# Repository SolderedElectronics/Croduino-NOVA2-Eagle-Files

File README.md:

# Croduino NOVA2 Eagle Files
## Image

[Croduino NOVA(222067)](https://e-radionica.com/en/croduino-nova2.html)

## Description and details
The Croduino NOVA2 is a microcontroller board with the ability to connect to a WiFi network and the Internet! It is based on an already well-known ESP8266 which is otherwise quite complicated to use on its own. With Nova, simply connect the board to USB and start programming your next IoT project. In addition, the microcontroller boards ideally suited for breadboard, which makes prototyping is even faster. Connecting the physical world with the internet has never been easier.

The brain of these boards is already mentioned Espressif's ESP826. Comes with full WiFi (both client and server side) and an integrated TCP / IP stack that supports DNS! Most importantly - programmable from Arduino IDE, there is no need to manually reset the board. The 80MHz frequency processor has as much as 1MB of space for your code (0.8MB available, bootloader 0.2MB) and 82kB of RAM (of which you can use 49kB). The board supports I2C, SPI and serial communications and has 9 GPIO pins, all of which support PWM and one analog input. In addition to the above, the board uses CH340 as a USB 2.0 interface, 3.3V voltage regulator, 4 LEDs, FCC and CE certificate, and a lot more. There is also an easyC connector on the board, which allows easy connection of various devices (available in e-radionica's offer) with a board. Finally, there is a standard JST lithium-ion connector for your project to be truly wireless. When you need to charge a battery, just plug in the USB cable and charge the battery with the integrated charger on the board. In detail:

- ESP8266 in ESP-12 package
- 80MHz, 1MB flash, 82kB RAM
- programmable from Arduina!
- 9 GPIO pins of which all support PWM
- 1 analog input(ADC), max. voltage 1V i 5V
- I2C, SPI, serial communication
- CH340 USB to UART bridge with micro USB connector
- 3.3V voltage regulator
- LEDs: power, tx, rx, GPIO13
- automatical hardware reset before upload of code
- two pushbuttons: reset i GPIO0
- comes with micro USB cable
- FCC i CE certificates for ESP-12

ESP8266 on-board is loaded with default bootloader.

## Repository content
This repo contains Cadsoft Eagle .sch and .brd files for Croduino NOVA board. It also contains schematic in .pdf created from .sch Eagle file. 
Files have been arranged into folders for navigating between different versions of board. 
Tip: layer 200 shows top silkscreen and layer 208 should be bottom silkscreen. tParts and bParts layers are not used.

## Docs
- [Croduino NOVA 2product page] (https://e-radionica.com/en/croduino-nova2.html)

## Board versions
- v1.0 - inital published version 

## License info
This product is open-source. Yay!
For any tech questions, contact us at techsupport@e-radionica.com
If you find an Issue, please open one at GitHub. If you can improve our product, fork us.

e-radionica.com Team.

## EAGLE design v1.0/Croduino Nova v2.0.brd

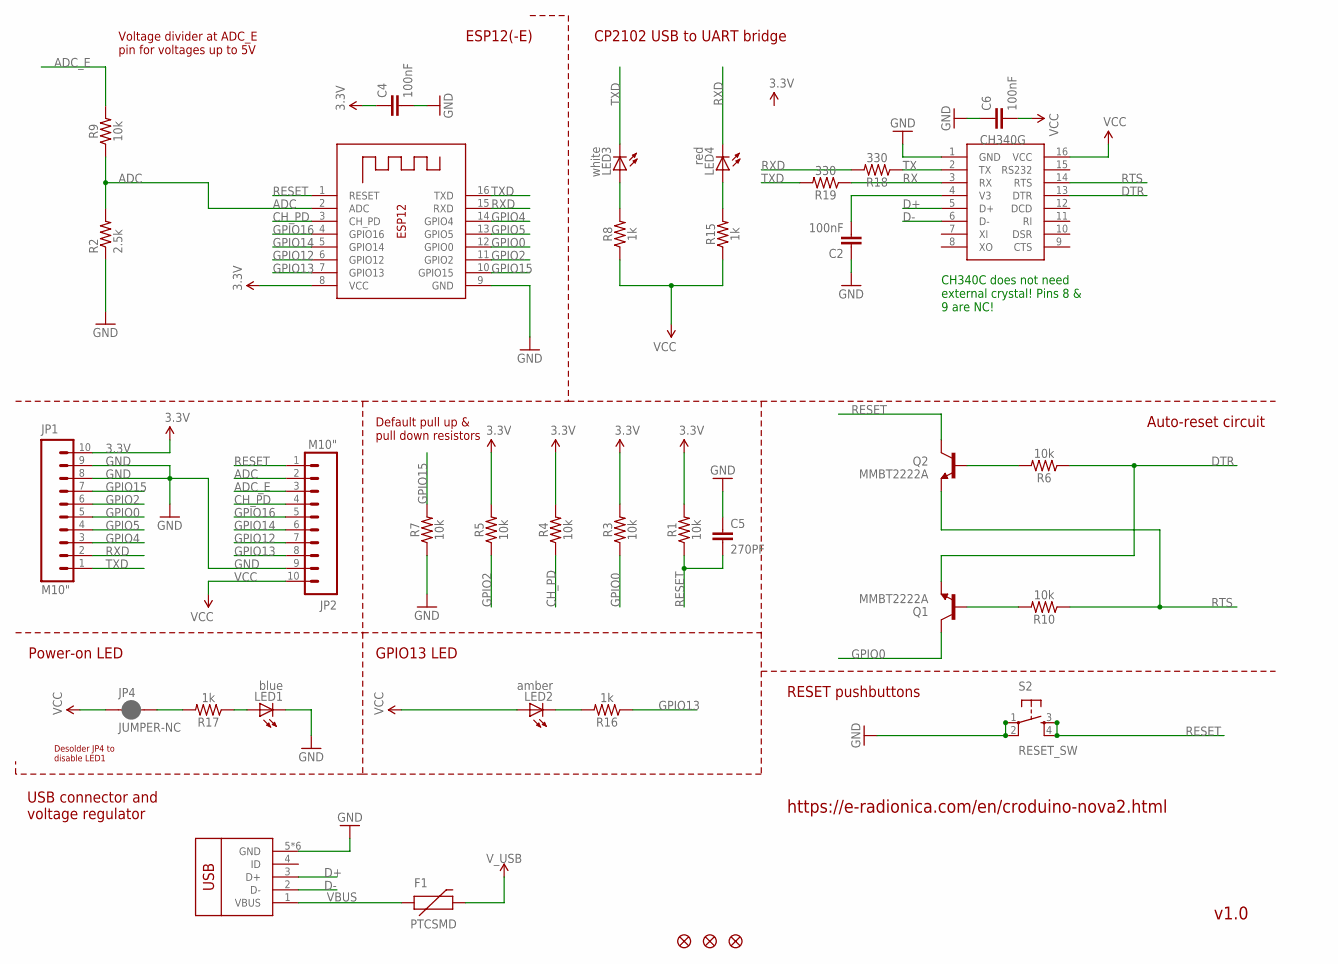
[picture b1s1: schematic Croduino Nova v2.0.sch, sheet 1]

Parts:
C2, C4, C6: 100nF; 0603-CAP
C5: 270PF; 0603
F1: PTCSMD; PTC-1206
JP1, JP2: M10"; 1X10
JP3, JP5, JP6: FIDUCIAL1X2; FIDUCIAL-1X2
JP4: JUMPER-NC; SMT-JUMPER_2_NC_PASTE_NO-SILK
LED1: blue; CHIP-LED0805
LED2: amber; CHIP-LED0805
LED3: white; CHIP-LED0805
LED4: red; CHIP-LED0805
Q1, Q2: MMBT2222A; SOT23-3
R1, R3, R4, R5, R6, R7, R9, R10: 10k; 0603
R2: 2.5k; 0603-RES
R8, R15, R16, R17: 1k; 0603
R18, R19: 330; 0603
S2: RESET_SW; TACTILE_SWITCH_SMD
U$8: USB-MICRO; U-F-M5DD-Y-L
U$10: CH340C; SOIC16
X1: ESP8266-12; ESP-12

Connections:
3.3V: C4.1, JP1.10, R1.2, R3.2, R4.2, R5.2, X1.8 (VCC); also elsewhere on the board
ADC: JP2.2, R2.2, R9.1, X1.2 (ADC)
ADC_E: JP2.3, R9.2
CH_PD: JP2.4, R4.1, X1.3 (CH_PD)
D+: U$8.3 (D+), U$10.5 (D+)
D-: U$8.2 (D-), U$10.6 (D-)
DTR: Q1.2 (E), R6.1, U$10.13 (DTR)
GND: C2.1, C4.2, C5.1, C6.1, JP1.8, JP1.9, JP2.9, LED1.C, R2.1, R7.1, S2.1, S2.2, U$8.5 (GND), U$8.PAD (GND), U$8.SHIELD1 (GND), U$8.SHIELD2 (GND), U$8.SHIELD3 (GND), U$8.SHIELD4 (GND), U$10.1 (GND), X1.9 (GND); also elsewhere on the board
GPIO0: JP1.5, Q1.3 (C), R3.1, X1.12 (GPIO0)
GPIO2: JP1.6, R5.1, X1.11 (GPIO2)
GPIO4: JP1.3, X1.14 (GPIO4); also elsewhere on the board
GPIO5: JP1.4, X1.13 (GPIO5); also elsewhere on the board
GPIO12: JP2.7, X1.6 (GPIO12)
GPIO13: JP2.8, R16.1, X1.7 (GPIO13)
GPIO14: JP2.6, X1.5 (GPIO14)
GPIO15: JP1.7, R7.2, X1.10 (GPIO15)
GPIO16: JP2.5, X1.4 (GPIO16)
unnamed: LED3.A, R8.2
unnamed: JP4.2, R17.2
unnamed: LED1.A, R17.1
unnamed: LED4.A, R15.2
unnamed: LED2.C, R16.2
unnamed: C2.2, U$10.4 (V3)
unnamed: Q1.1 (B), R10.2
unnamed: Q2.1 (B), R6.2
RESET: C5.2, JP2.1, Q2.3 (C), R1.1, S2.3, S2.4, X1.1 (RESET)
RTS: Q2.2 (E), R10.1, U$10.14 (RTS)
RX: R19.1, U$10.3 (RX)
RXD: JP1.2, LED4.C, R18.2, X1.15 (RXD)
TX: R18.1, U$10.2 (TX)
TXD: JP1.1, LED3.C, R19.2, X1.16 (TXD)
VBUS: F1.1, U$8.1 (VBUS)
VCC: C6.2, JP2.10, JP4.1, LED2.A, R8.1, R15.1, U$10.16 (VCC); also elsewhere on the board
V_USB: F1.2; also elsewhere on the board

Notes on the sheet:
USB connector and voltage regulator
Power-on LED
GPIO13 LED
Desolder JP4 to disable LED1
ESP12(-E)
CP2102 USB to UART bridge
Voltage divider at ADC_E pin for voltages up to 5V
Default pull up & pull down resistors
Auto-reset circuit
RESET pushbuttons
https://e-radionica.com/en/croduino-nova2.html
v1.0
CH340C does not need external crystal! Pins 8 & 9 are NC!

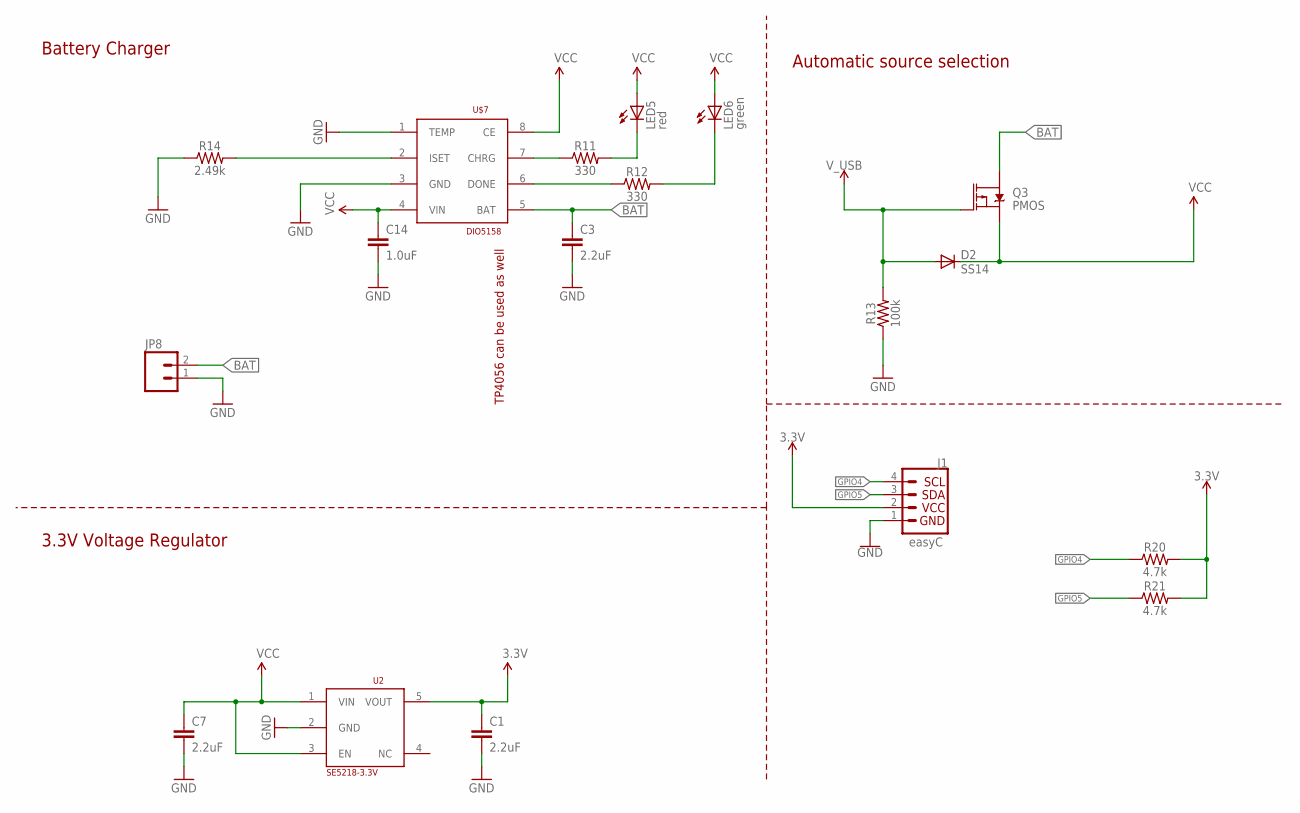
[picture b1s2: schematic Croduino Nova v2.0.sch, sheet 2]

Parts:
C1, C3, C7: 2.2uF; 0603
C14: 1.0uF; 0603
D2: SS14; DO-214AC
J1: QWIIC_CONNECTORJS-1MM; 1X04_1MM_RA
JP8: M02-JST-2MM-SMT; JST-2-SMD
LED5: red; CHIP-LED0805
LED6: green; CHIP-LED0805
Q3: PMOS; SOT23-3
R11, R12: 330; 0603
R13: 100k; 0603
R14: 2.49k; 0603
R20, R21: 4.7k; 0603
U2: SE5218-3.3V; SOT23-5
U$7: DIO5158; SOIC-8

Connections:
3.3V: C1.1, J1.2, R20.2, R21.2, U2.5 (VOUT); also elsewhere on the board
BAT: C3.1, JP8.2, Q3.3 (D), U$7.5 (BAT)
CHRG: R11.1, U$7.7 (CHRG)
DONE: R12.1, U$7.6 (DONE)
GND: C1.2, C3.2, C7.2, C14.2, J1.1, JP8.1, R13.1, R14.1, U2.2 (GND), U$7.1 (TEMP), U$7.3 (GND); also elsewhere on the board
GPIO4: J1.4, R20.1; also elsewhere on the board
GPIO5: J1.3, R21.1; also elsewhere on the board
ISET: R14.2, U$7.2 (ISET)
LED1: LED5.C, R11.2
LED2: LED6.C, R12.2
VCC: C7.1, C14.1, D2.C, LED5.A, LED6.A, Q3.2 (S), U2.1 (VIN), U2.3 (EN), U$7.4 (VIN), U$7.8 (CE); also elsewhere on the board
V_USB: D2.A, Q3.1 (G), R13.2; also elsewhere on the board

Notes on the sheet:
TP4056 can be used as well
3.3V Voltage Regulator
Battery Charger
Automatic source selection
easyC

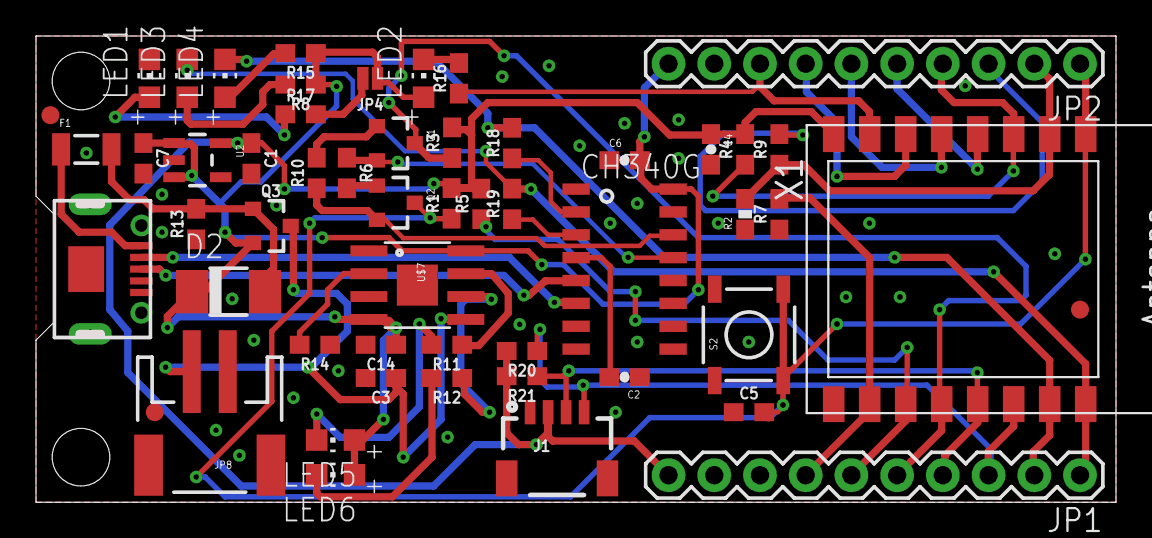
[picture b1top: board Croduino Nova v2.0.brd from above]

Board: 2 copper layers, 60.0 x 25.9 mm, 60 parts (0 on the bottom side), 40 nets.

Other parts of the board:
U$1: LOGO-3MM
U$3: OSH-3MM
U$4: E-R.IO-6MM
U$5: MADE-IN-CROATIA-10MM
U$6: EASYC
U$9: CRODUINO_NOVA_V2.0

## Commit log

2018-11-26 Initial
2018-11-26 init

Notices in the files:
parts and their libraries:
SparkFun: Licensing: CC v3.0 Share-Alike You are welcome to use this library for commercial purposes.
SparkFun-Resistors: Licensing: Creative Commons ShareAlike 4.0 International - https://creativecommons.org/licenses/by-sa/4.0
